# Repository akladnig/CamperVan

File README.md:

# CamperVan Design and Arduino Circuit Design

<!--toc:start-->
- [CamperVan Design and Arduino Circuit Design](#campervan-design-and-arduino-circuit-design)
  - [Campervan Design Overview](#campervan-design-overview)
  - [Dashboard App](#dashboard-app)
  - [Electrical System](#electrical-system)
    - [Sensors](#sensors)
  - [Circuit Design](#circuit-design)
    - [Battery and voltage monitoring](#battery-and-voltage-monitoring)
      - [Voltage Divider Design](#voltage-divider-design)
      - [Low Pass Filter](#low-pass-filter)
  - [TODO](#todo)
<!--toc:end-->

## Campervan Design Overview
I used [OpenScad](https://openscad.org/) to do the campervan design. Whilst I have used SketchUp in the past OpenScad appealed to me more as it is a programmers CAD program plus it is a parametric CAD program which allow me to quickly change a parameter to see how it affects the van layout e.g. visualising the Sofa Bed as a Sofa or a Bed, or easily changing the width of a cupboard, which would cause all other dependent cupboards to adjust accordingly.

## Dashboard App
The dashboard app on ios/macos to control the electrical system is written in Flutter and communicates to the Arduino control board via websockets. See [Campervan Flutter](https://github.com/akladnig/campervan_flutter) for details.

## Electrical System

The electrical system for the camper van needs to power the following devices:
- Induction Cooktop - 1800W
- Air Fryer - 1800W
- Duetto Hot Water - 300W
- Bushman 85l fridge -
- Water Pump -
- Lights & Fan - 

The power system needs to provide off-grid power for 3 days, which required a 4.8kW or 400Ah battery system.

Since 12V, 400A would require massive fuses, switches and cable etc. I've decided to run the system as 2x isolated batteries, rather than in parallel. This will reduce the need for 400A fuses and switches to 200A fuses ans switches.

The other issue is that the DC-DC battery charger has a maximum output of 50A which would result in a 7-8 hour charge time via the alternator. Being able to independently charge each battery with it's own battery charger solves this problem and also 2x 50A chargers are a lot cheaper than a single 100A charger.

The system is designed so the batteries can never be inadvertently connected in parallel.

There are two modes of operation:
- Manual
- Automatic

Manual mode will override any automatic setting and allows the selection of:
- which battery to use for powering appliances
- swapping the dc-dc battery chargers. This will allow selection of which battery to charge via Solar Cells/50A DC-DC charger or 20A DC-DC charger.

Automatic mode will select the battery to use for powering appliances. When the battery charge falls below a certain threshold it will swap to the other battery.

Automatic mode will also swap chargers during driving to ensure the optimum charge time for both batteries. When the ignition is off, charging via solar cells will automatically switch to the second battery when the first is fully charged.

### Sensors
There are a variety of sensors in use:
- voltage dividers
- RS485 which will require some reverse engineering
- Hall effect devices
- Bluetooth for the smart batteries and 50A DC-DC

The following devices are monitored for the associated properties using a voltage divider:
- Starter Battery voltage
- Battery 1 input voltage (before 60A fuse)
- Battery 1 output voltage (after 200A fuse)
- Battery 2 input voltage (before 60A fuse)
- Battery 2 output voltage (after 200A fuase)
- Battery 2 charge switch status - to a digital input
- Battery 2 switch status - to a digital input

The following are monitored via RS485:
- 20A DC-DC battery charger
- Duoetto Heater

The following are monitored via hall effect devices:
- Water input flow
- Water output flow

The following devices are bluetooth enabled:
- Battery 1
- Battery 2
- 50A DC-DC charger

Schematic design software used is [Kicad](https://www.kicad.org/)

## Circuit Design
### General Design requirements
- All inputs and outputs of the main management module to be optically isolated to prevent any issues with voltage spikes damaging the module and to also reduce any potential issues with ground loops and noise.

### Battery and voltage monitoring
#### Linear OptoCoupler Design
An IL300 linear opto-coupler is used to monitor the voltage of the following:
- Starter Battery
- Battery 1
- Battery 2

#### Voltage Divider Design
The typical battery voltage ranges from 10.0V - 14.4V and the maximum input voltage levels are ether 3.3V or 5V depending on the Arduino device used.
In order to keep power consumption low large value resistors in the 100k range will be used. But with such large values noise increases (Johnson noise) and the inputs to the ADC on the Arduino or external ADC (MCP3008 or MCP3208) require a low impedance source so a unity gain low pass filter will be required.

Equation for the voltage divider is:

R1 = R2(Vin - Vout)/Vout

Using an input voltage of 15.0V and choosing R2 = 100k
Gives:

- R1 = 357k 1% for a 3.3V output
- R1 = 200k 1% for a 5V output

#### Low Pass Filter
A simple 2 pole Butterworth low pass filter will be used.
A quick web search shows that a 0.1Hz - 1Hz filter should be used, which sounds reasonable to me. I'll use 1Hz to keep the capacitor value on the lower end.

Formula for a low pass filter is:
- RC = 1/(2\*pi\*Cn\*f)

Cn and K are constants that are used to set various low pass filter types. For a 2 pole Butterworth the values are:
- Cn = 1
- K = 1.586

Refer to "The Art of Electronics page 408".

For:
- f = 1Hz
- C = 1uF

Gives:
- R = 154k 1%
- Rga = (K-1)R = 5k9 1% 

## TODO
 - add an Oled touch panel
 - ignition switch input

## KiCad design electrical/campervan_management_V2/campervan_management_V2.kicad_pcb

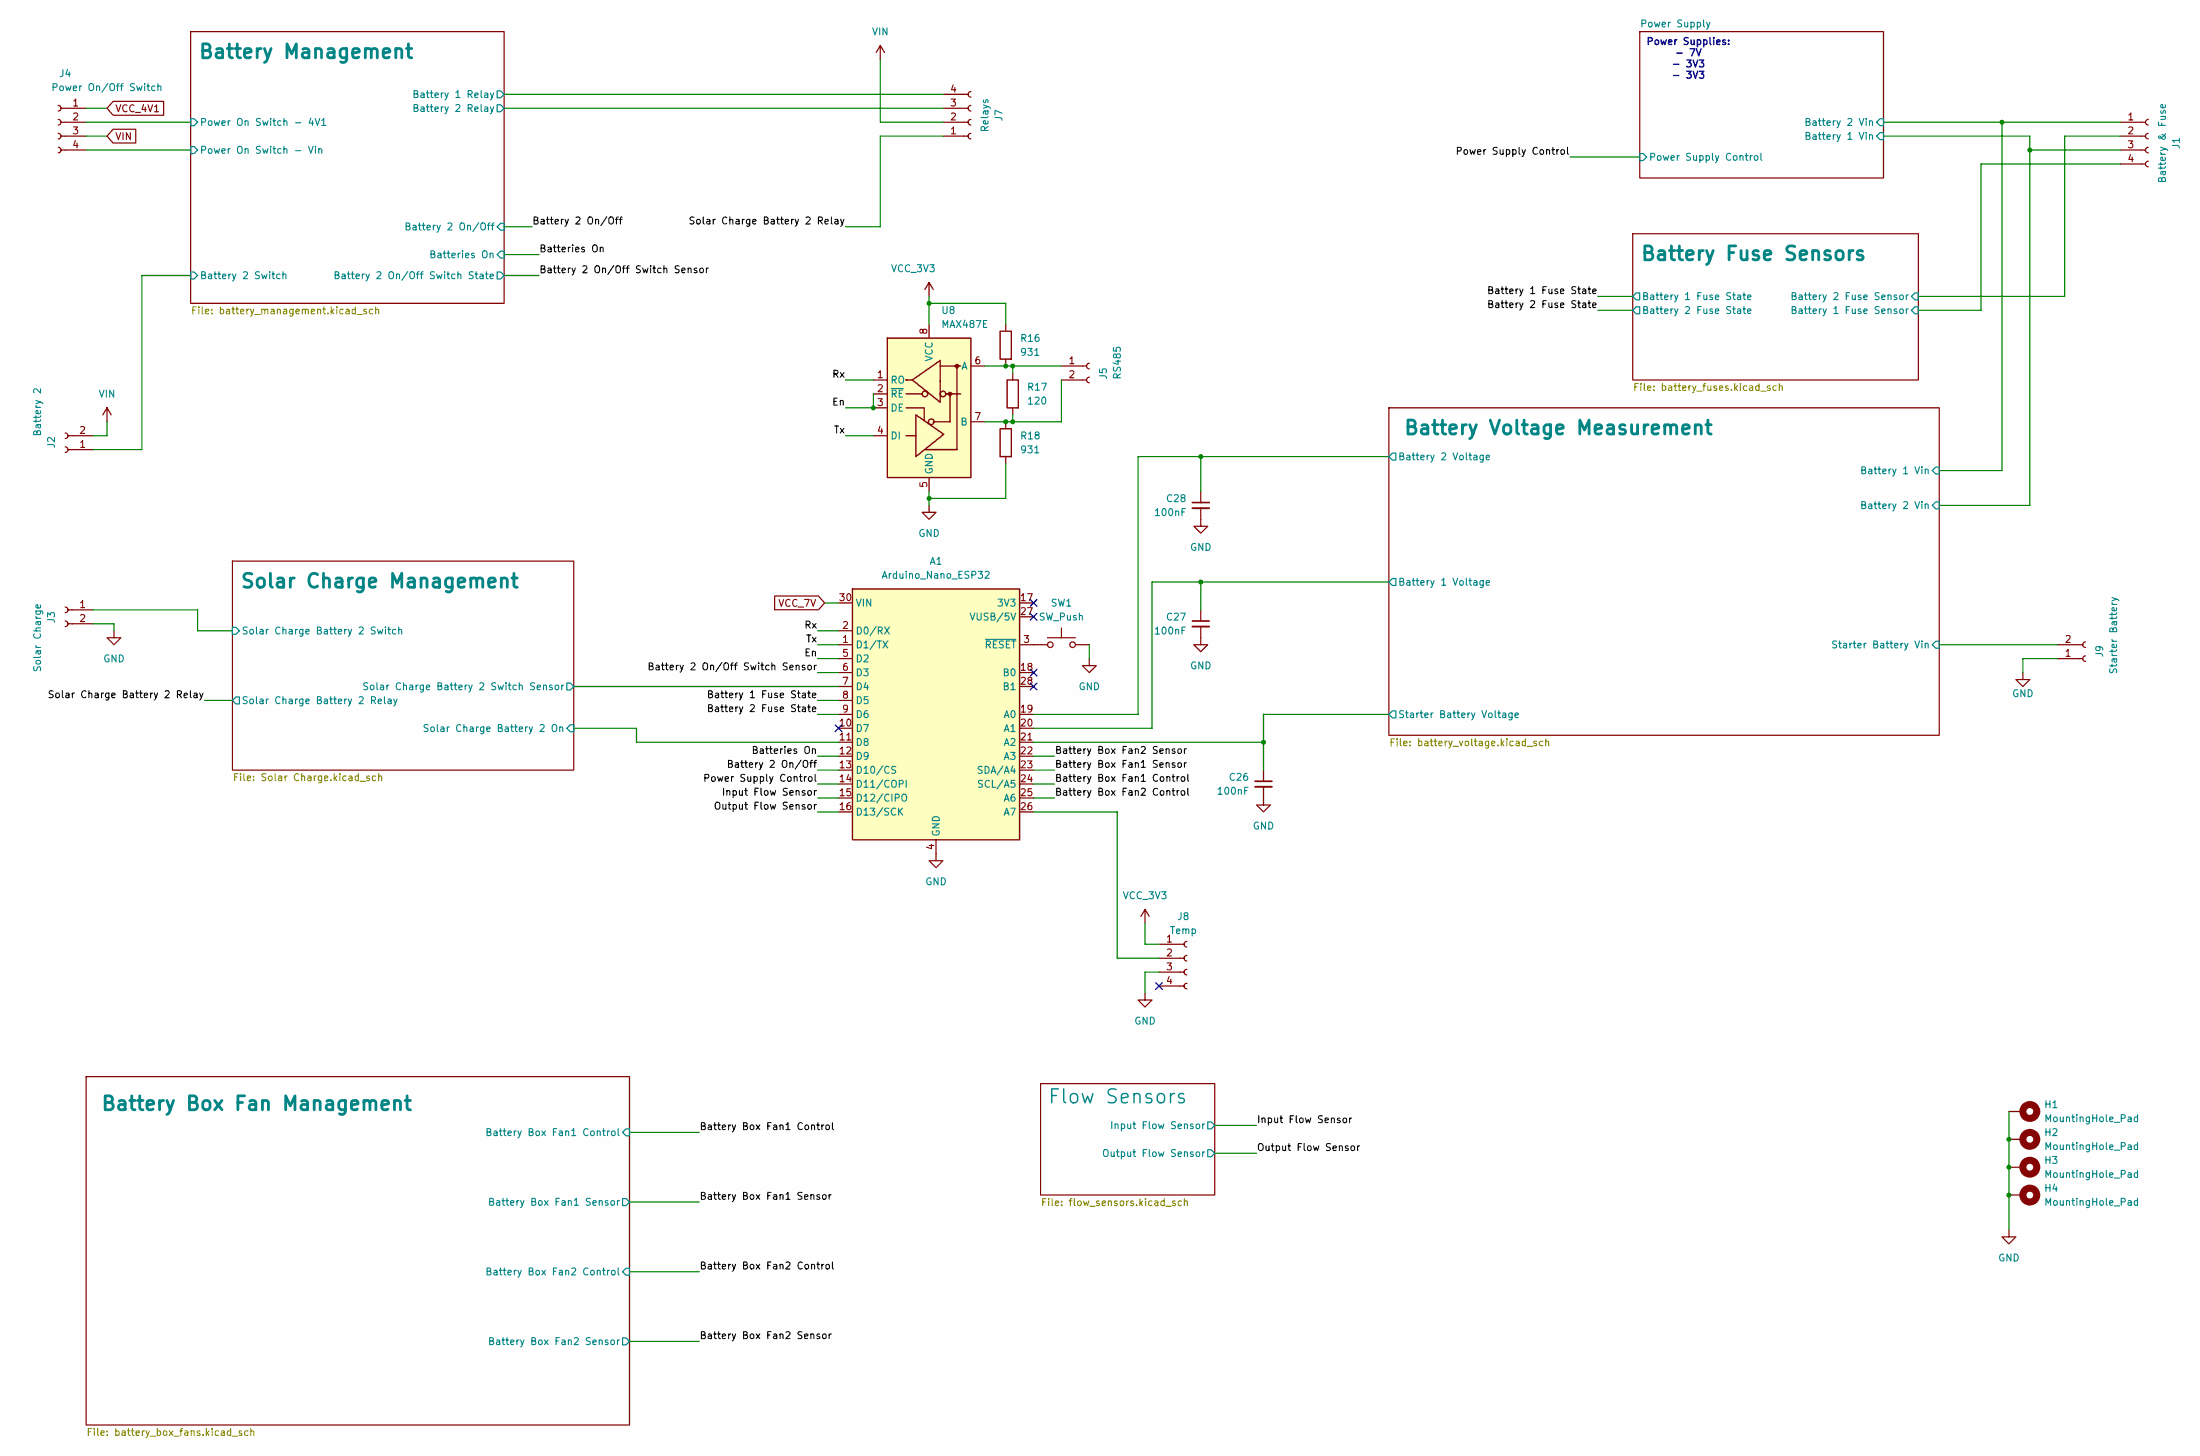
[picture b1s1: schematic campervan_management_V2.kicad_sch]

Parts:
A1: Arduino_Nano_ESP32; Arduino_Nano
C26, C27, C28: 100nF; C_0805_2012Metric; LCSC PN C28233
H1, H2, H3, H4: MountingHole_Pad; MountingHole_4.3mm_M4_Pad
J1: Battery & Fuse; Molex_Mini-Fit_Jr_5566-04A_2x02_P4.20mm_Vertical
J2: Battery 2; Molex_Mini-Fit_Jr_5566-02A_2x01_P4.20mm_Vertical
J3: Solar Charge; Molex_Mini-Fit_Jr_5566-02A_2x01_P4.20mm_Vertical
J4: Power On/Off Switch; Molex_Mini-Fit_Jr_5566-04A_2x02_P4.20mm_Vertical
J5: RS485; Molex_Mini-Fit_Jr_5566-02A_2x01_P4.20mm_Vertical
J7: Relays; Molex_Mini-Fit_Jr_5566-04A_2x02_P4.20mm_Vertical
J8: Temp; Molex_Mini-Fit_Jr_5566-04A_2x02_P4.20mm_Vertical
J9: Starter Battery; Molex_Mini-Fit_Jr_5566-02A_2x01_P4.20mm_Vertical
R16, R18: 931; R_0805_2012Metric
R17: 120; R_0805_2012Metric; LCSC PN C17437
SW1: SW_Push; SW_SPST_JLC; LCSC PN C720477
U8: MAX487E; SOIC-8_3.9x4.9mm_P1.27mm; LCSC PN C116539

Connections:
/Batteries On: A1.12 (D9); also elsewhere on the board
/Battery 1 Fuse State: A1.8 (D5); also elsewhere on the board
/Battery 2 Fuse State: A1.9 (D6); also elsewhere on the board
/Battery 2 On/Off: A1.13 (D10/CS); also elsewhere on the board
/Battery 2 On/Off Switch Sensor: A1.6 (D3); also elsewhere on the board
/Battery Box Fan1 Control: A1.24 (SCL/A5); also elsewhere on the board
/Battery Box Fan1 Sensor: A1.23 (SDA/A4); also elsewhere on the board
/Battery Box Fan2 Control: A1.25 (A6); also elsewhere on the board
/Battery Box Fan2 Sensor: A1.22 (A3); also elsewhere on the board
/Battery Fuse Sensors/Battery 1 Fuse Sensor: J1.4; also elsewhere on the board
/Battery Fuse Sensors/Battery 2 Fuse Sensor: J1.2; also elsewhere on the board
/Battery Management/Battery 1 Relay: J7.4; also elsewhere on the board
/Battery Management/Battery 2 Relay: J7.3; also elsewhere on the board
/Battery Management/Battery 2 Switch: J2.1; also elsewhere on the board
/Battery Management/Power On Switch - 4V1: J4.2; also elsewhere on the board
/Battery Management/Power On Switch - Vin: J4.4; also elsewhere on the board
/Battery Voltage Measurement/Battery 1 Vin: J1.1; also elsewhere on the board
/Battery Voltage Measurement/Battery 1 Voltage: A1.20 (A1), C27.1; also elsewhere on the board
/Battery Voltage Measurement/Battery 2 Vin: J1.3; also elsewhere on the board
/Battery Voltage Measurement/Battery 2 Voltage: A1.19 (A0), C28.1; also elsewhere on the board
/Battery Voltage Measurement/Starter Battery Vin: J9.2; also elsewhere on the board
/Battery Voltage Measurement/Starter Battery Voltage: A1.21 (A2), C26.1; also elsewhere on the board
/En: A1.5 (D2), U8.2 (~RE), U8.3 (DE)
/Input Flow Sensor: A1.15 (D12/CIPO); also elsewhere on the board
/Output Flow Sensor: A1.16 (D13/SCK); also elsewhere on the board
/Power Supply Control: A1.14 (D11/COPI); also elsewhere on the board
/Rx: A1.2 (D0/RX), U8.1 (RO)
/Solar Charge Battery 2 Relay: J7.1; also elsewhere on the board
/Solar Charge Management/Solar Charge Battery 2 On: A1.11 (D8); also elsewhere on the board
/Solar Charge Management/Solar Charge Battery 2 Switch: J3.1; also elsewhere on the board
/Solar Charge Management/Solar Charge Battery 2 Switch Sensor: A1.7 (D4); also elsewhere on the board
/Tx: A1.1 (D1/TX), U8.4 (DI)
GND: A1.4 (GND), A1.29 (GND), C26.2, C27.2, C28.2, H1.1, H2.1, H3.1, H4.1, J3.2, J8.3, J9.1, R18.2, SW1.2, U8.5 (GND); also elsewhere on the board
unnamed: A1.26 (A7), J8.2
unnamed: A1.3 (~RESET), SW1.1
unnamed: J5.1, R16.2, R17.1, U8.6 (A)
unnamed: J5.2, R17.2, R18.1, U8.7 (B)
VCC_3V3: J8.1, R16.1, U8.8 (VCC); also elsewhere on the board
VCC_4V1: J4.1; also elsewhere on the board
VCC_7V: A1.30 (VIN); also elsewhere on the board
VIN: J2.2, J4.3, J7.2; also elsewhere on the board

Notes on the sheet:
Power Supplies: - 7V - 3V3 - 3V3

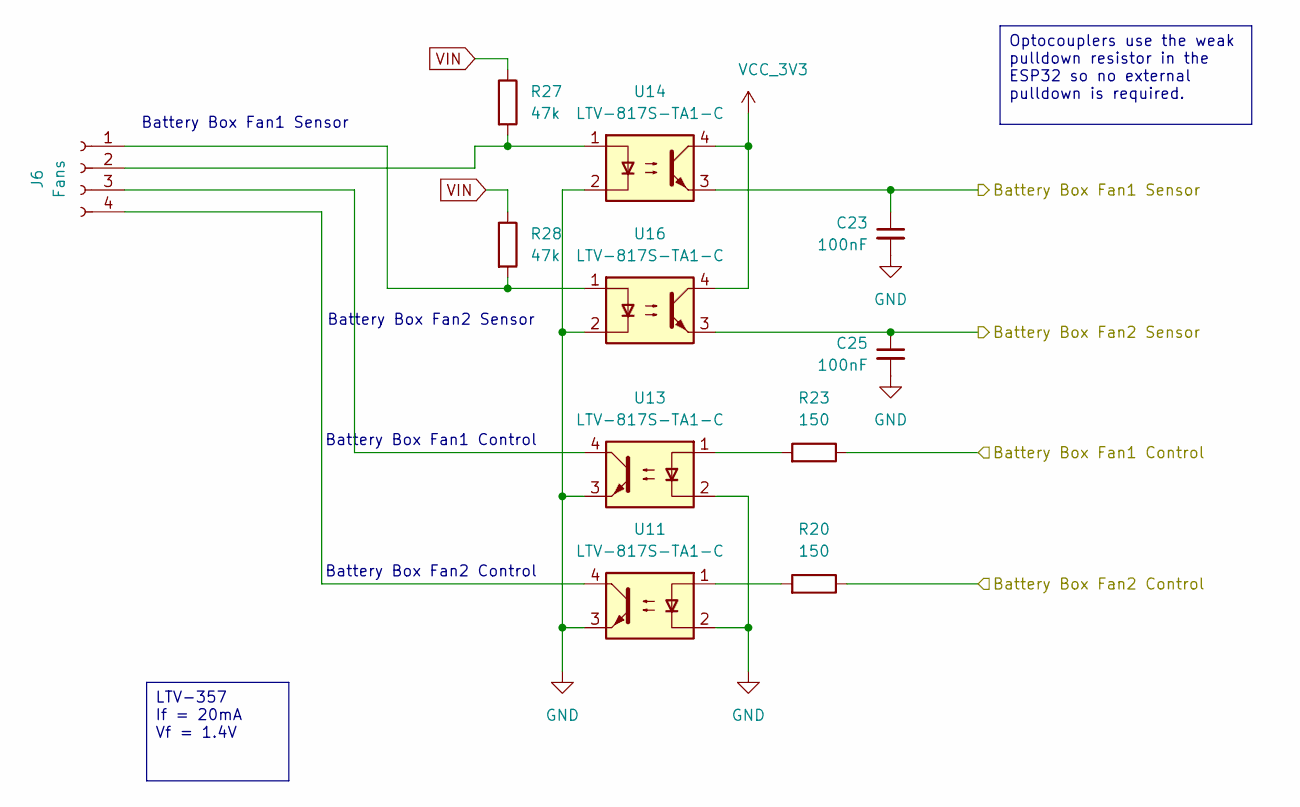
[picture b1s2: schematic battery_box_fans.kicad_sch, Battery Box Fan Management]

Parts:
C23, C25: 100nF; C_0805_2012Metric; LCSC PN C28233
J6: Fans; Molex_Mini-Fit_Jr_5566-04A_2x02_P4.20mm_Vertical
R20, R23: 150; R_0805_2012Metric; LCSC PN C17471
R27, R28: 47k; R_0805_2012Metric; LCSC PN C17713
U11, U13, U14, U16: LTV-817S-TA1-C; SO-4_4.4x3.6mm_P2.54mm; LCSC PN C109227

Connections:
/Battery Box Fan1 Control: R23.1; also elsewhere on the board
/Battery Box Fan1 Sensor: C23.1, U14.3; also elsewhere on the board
/Battery Box Fan2 Control: R20.1; also elsewhere on the board
/Battery Box Fan2 Sensor: C25.1, U16.3; also elsewhere on the board
GND: C23.2, C25.2, U11.2, U11.3, U13.2, U13.3, U14.2, U16.2; also elsewhere on the board
unnamed: J6.1, R28.2, U16.1
unnamed: J6.2, R27.2, U14.1
unnamed: J6.3, U13.4
unnamed: J6.4, U11.4
unnamed: R20.2, U11.1
unnamed: R23.2, U13.1
VCC_3V3: U14.4, U16.4; also elsewhere on the board
VIN: R27.1, R28.1; also elsewhere on the board

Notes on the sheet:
Battery Box Fan2 Control
Battery Box Fan1 Control
Battery Box Fan2 Sensor
Battery Box Fan1 Sensor
Optocouplers use the weak pulldown resistor in the ESP32 so no external pulldown is required.
LTV-357 If = 20mA Vf = 1.4V

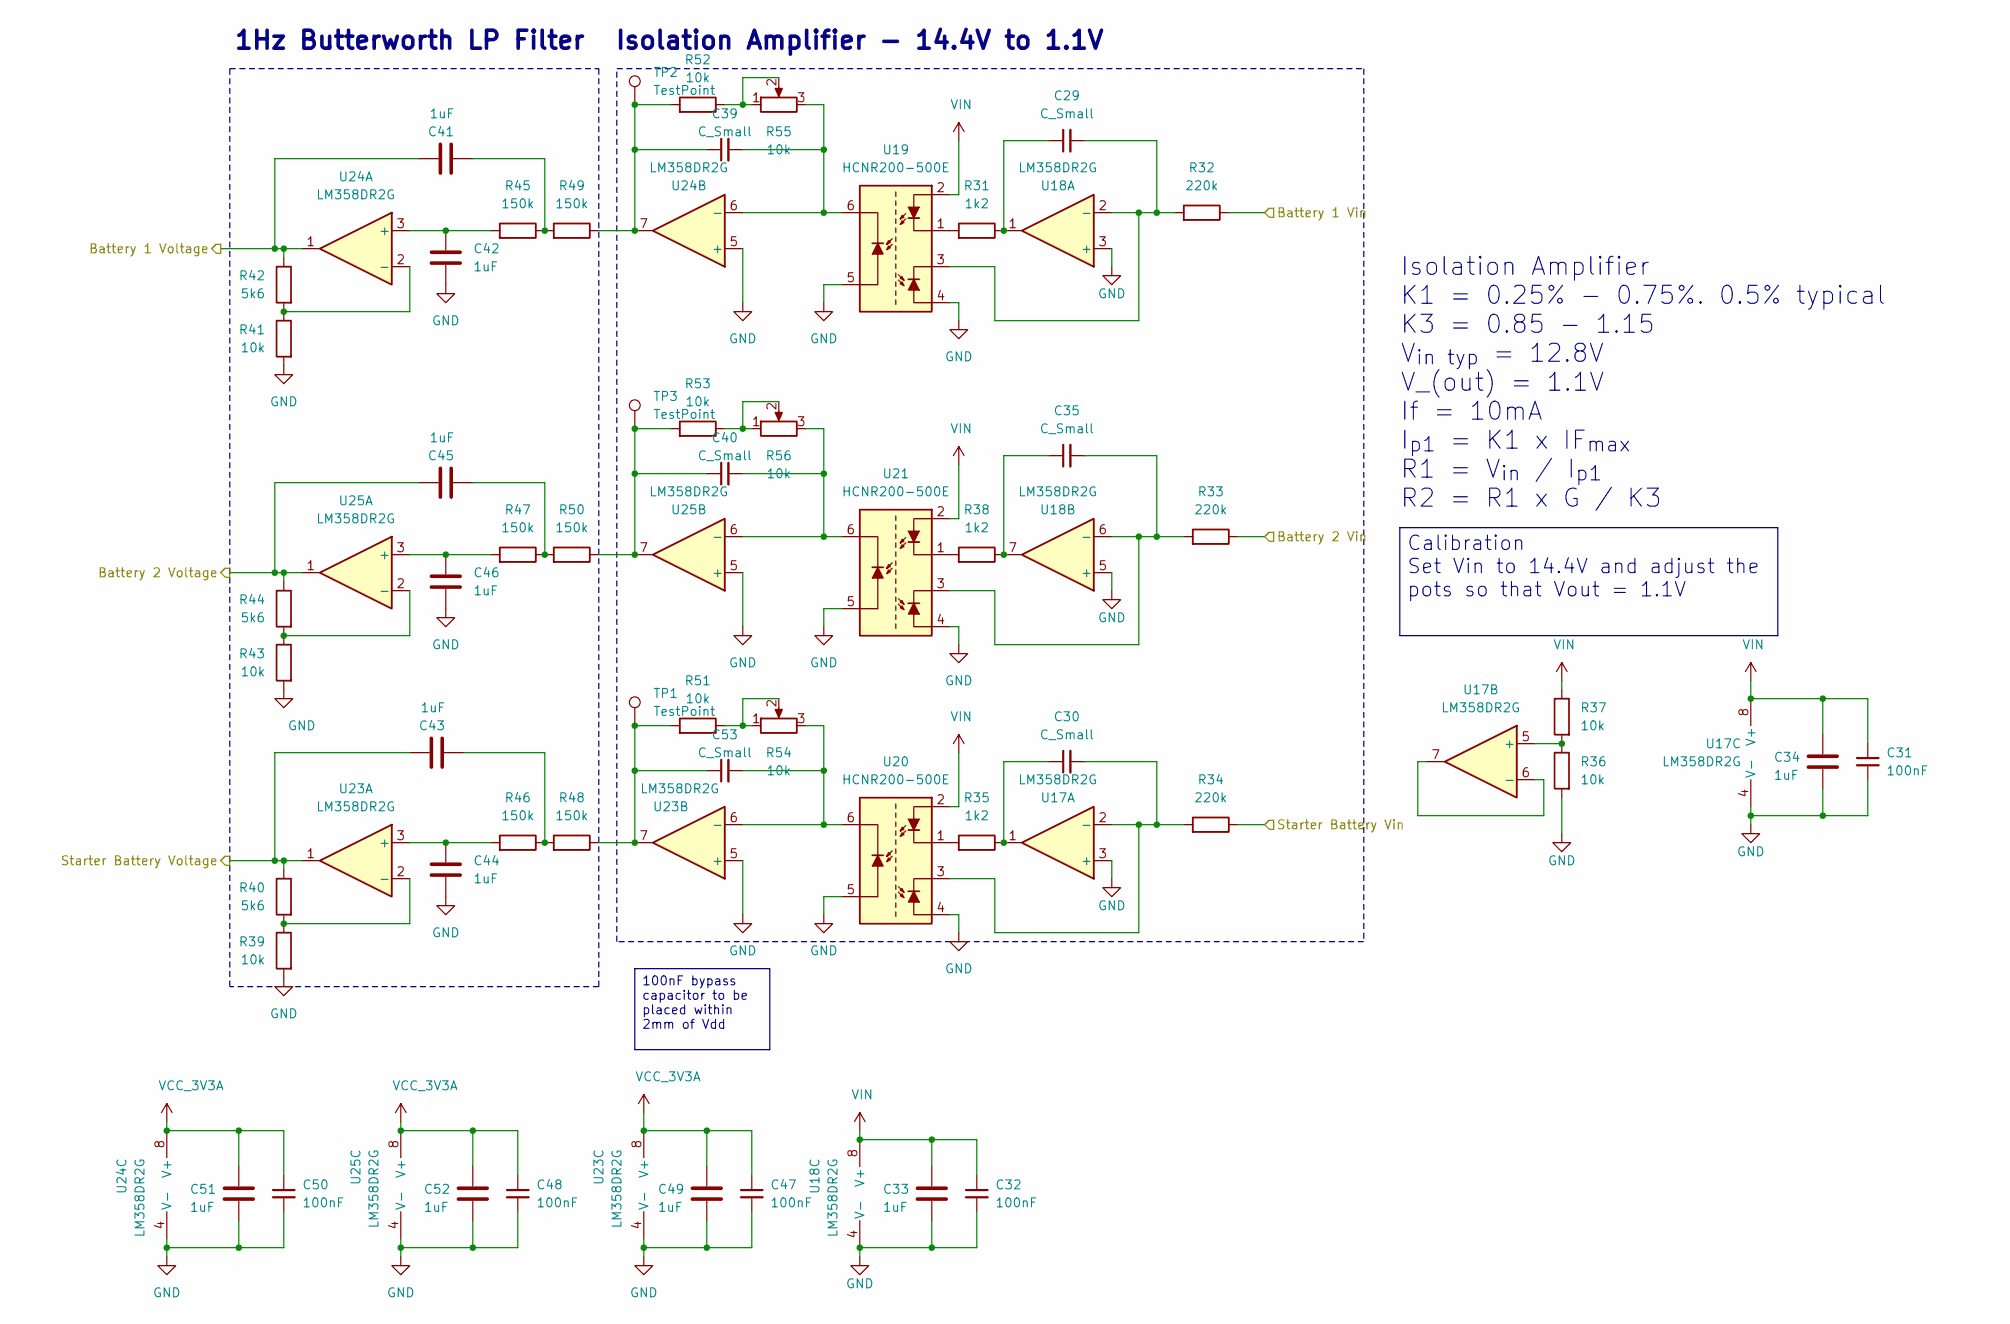
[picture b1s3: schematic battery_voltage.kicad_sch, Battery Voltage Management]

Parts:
C29, C30, C35, C39, C40, C53: C_Small; C_0603_1608Metric
C31, C32, C47, C48, C50: 100nF; C_0805_2012Metric; LCSC PN C28233
C33, C34, C41, C42, C43, C44, C45, C46, C49, C51, C52: 1uF; C_0603_1608Metric; LCSC PN C15849
R31, R35, R38: 1k2; R_0603_1608Metric; LCSC PN C22765
R32, R33, R34: 220k; R_0603_1608Metric; LCSC PN C22967
R36, R37, R39, R41, R43, R51, R52, R53: 10k; R_0603_1608Metric; LCSC PN C25804
R40, R42, R44: 5k6; R_0603_1608Metric; LCSC PN C23189
R45, R46, R47, R48, R49, R50: 150k; R_0603_1608Metric; LCSC PN C22807
R54, R55, R56: 10k; Potentiometer_Bourns_3296W_Vertical
TP1, TP2, TP3: TestPoint; 5000
U17, U18, U23, U24, U25: LM358DR2G; SOIC-8_ONS-L; LCSC PN C7950
U19, U20, U21: HCNR200-500E; SMDIP-8_W11.48mm; LCSC PN C23785

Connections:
/Battery Voltage Measurement/Battery 1 Vin: R32.1; also elsewhere on the board
/Battery Voltage Measurement/Battery 1 Voltage: C41.2, R42.1, U24.1; also elsewhere on the board
/Battery Voltage Measurement/Battery 2 Vin: R33.1; also elsewhere on the board
/Battery Voltage Measurement/Battery 2 Voltage: C45.2, R44.1, U25.1; also elsewhere on the board
/Battery Voltage Measurement/Starter Battery Vin: R34.1; also elsewhere on the board
/Battery Voltage Measurement/Starter Battery Voltage: C43.2, R40.1, U23.1; also elsewhere on the board
GND: C31.2, C32.2, C33.2, C34.2, C42.2, C44.2, C46.2, C47.2, C48.2, C49.2, C50.2, C51.2, C52.2, R36.2, R39.2, R41.2, R43.2, U17.3 (+), U17.4 (V-), U18.3 (+), U18.4 (V-), U18.5 (+), U19.4, U19.5, U20.4, U20.5, U21.4, U21.5, U23.4 (V-), U23.5 (+), U24.4 (V-), U24.5 (+), U25.4 (V-), U25.5 (+); also elsewhere on the board
unnamed: C29.1, R31.1, U18.1
unnamed: C30.1, R35.1, U17.1
unnamed: C35.1, R38.1, U18.7
unnamed: C39.1, R49.1, R52.2, TP2.1, U24.7
unnamed: C40.1, R50.1, R53.2, TP3.1, U25.7
unnamed: C41.1, R45.1, R49.2
unnamed: C43.1, R46.1, R48.2
unnamed: C45.1, R47.1, R50.2
unnamed: C53.1, R48.1, R51.2, TP1.1, U23.7
unnamed: R31.2, U19.1
unnamed: R35.2, U20.1
unnamed: R38.2, U21.1
unnamed: R51.1, R54.1, R54.2
unnamed: R52.1, R55.1, R55.2
unnamed: R53.1, R56.1, R56.2
unnamed: C30.2, R34.2, U17.2 (-), U20.3
unnamed: R36.1, R37.2, U17.5 (+)
unnamed: U17.6 (-), U17.7
unnamed: C29.2, R32.2, U18.2 (-), U19.3
unnamed: C35.2, R33.2, U18.6 (-), U21.3
unnamed: C44.1, R46.2, U23.3 (+)
unnamed: R39.1, R40.2, U23.2 (-)
unnamed: C53.2, R54.3, U20.6, U23.6 (-)
unnamed: C42.1, R45.2, U24.3 (+)
unnamed: R41.1, R42.2, U24.2 (-)
unnamed: C39.2, R55.3, U19.6, U24.6 (-)
unnamed: C46.1, R47.2, U25.3 (+)
unnamed: R43.1, R44.2, U25.2 (-)
unnamed: C40.2, R56.3, U21.6, U25.6 (-)
VCC_3V3A: C47.1, C48.1, C49.1, C50.1, C51.1, C52.1, U23.8 (V+), U24.8 (V+), U25.8 (V+); also elsewhere on the board
VIN: C31.1, C32.1, C33.1, C34.1, R37.1, U17.8 (V+), U18.8 (V+), U19.2, U20.2, U21.2; also elsewhere on the board

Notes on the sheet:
Isolation Amplifier K1 = 0.25% - 0.75%. 0.5% typical K3 = 0.85 - 1.15 V_{in typ} = 12.8V V_(out) = 1.1V If = 10mA I_{p1} = K1 x IF_{max} R1 = V_{in} / I_{p1} R2 = R1 x G / K3
Isolation Amplifier - 14.4V to 1.1V
1Hz Butterworth LP Filter
100nF bypass capacitor to be placed within 2mm of Vdd
Calibration Set Vin to 14.4V and adjust the pots so that Vout = 1.1V

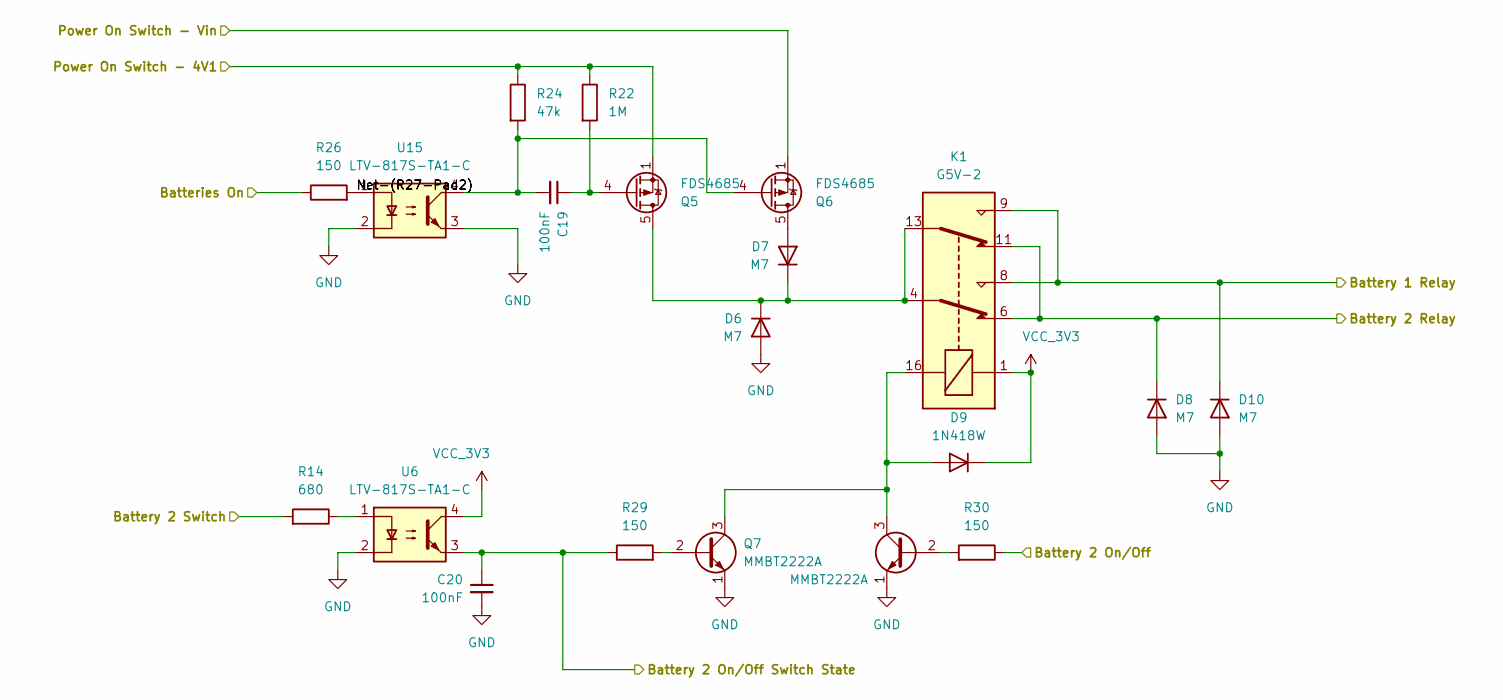
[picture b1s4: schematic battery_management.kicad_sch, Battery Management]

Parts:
C19, C20: 100nF; C_0805_2012Metric; LCSC PN C28233
D6, D7, D8, D10: M7; D_SMA; LCSC PN C95872
D9: 1N418W; D_SOD-123; LCSC PN C81598
K1: G5V-2; Relay_DPDT_Omron_G5V-2
Q5, Q6: FDS4685; SOIC-8_3.9x4.9mm_P1.27mm; LCSC PN C336026
Q7, Q8: MMBT2222A; SOT-23; LCSC PN C8512
R14: 680; R_0805_2012Metric; LCSC PN C17798
R22: 1M; R_0805_2012Metric; LCSC PN C17514
R24: 47k; R_0805_2012Metric; LCSC PN C17713
R26, R29, R30: 150; R_0805_2012Metric; LCSC PN C17471
U6, U15: LTV-817S-TA1-C; SO-4_4.4x3.6mm_P2.54mm; LCSC PN C109227

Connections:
/Batteries On: R26.1; also elsewhere on the board
/Battery 2 On/Off: R30.1; also elsewhere on the board
/Battery 2 On/Off Switch Sensor: C20.1, R29.1, U6.3; also elsewhere on the board
/Battery Management/Battery 1 Relay: D10.1 (K), K1.8, K1.9; also elsewhere on the board
/Battery Management/Battery 2 Relay: D8.1 (K), K1.6, K1.11; also elsewhere on the board
/Battery Management/Battery 2 Switch: R14.2; also elsewhere on the board
/Battery Management/Net-(R27-Pad2): R26.2, U15.1
/Battery Management/Power On Switch - 4V1: Q5.1 (S), Q5.2 (S), Q5.3 (S), R22.1, R24.1; also elsewhere on the board
/Battery Management/Power On Switch - Vin: Q6.1 (S), Q6.2 (S), Q6.3 (S); also elsewhere on the board
GND: C20.2, D6.2 (A), D8.2 (A), D10.2 (A), Q7.1 (E), Q8.1 (E), U6.2, U15.2, U15.3; also elsewhere on the board
unnamed: D6.1 (K), D7.1 (K), K1.4, K1.13, Q5.5 (D), Q5.6 (D), Q5.7 (D), Q5.8 (D)
unnamed: D7.2 (A), Q6.5 (D), Q6.6 (D), Q6.7 (D), Q6.8 (D)
unnamed: D9.2 (A), K1.16, Q7.3 (C), Q8.3 (C)
unnamed: C19.1, Q5.4 (G), R22.2
unnamed: C19.2, Q6.4 (G), R24.2, U15.4
unnamed: Q7.2 (B), R29.2
unnamed: Q8.2 (B), R30.2
unnamed: R14.1, U6.1
VCC_3V3: D9.1 (K), K1.1, U6.4; also elsewhere on the board

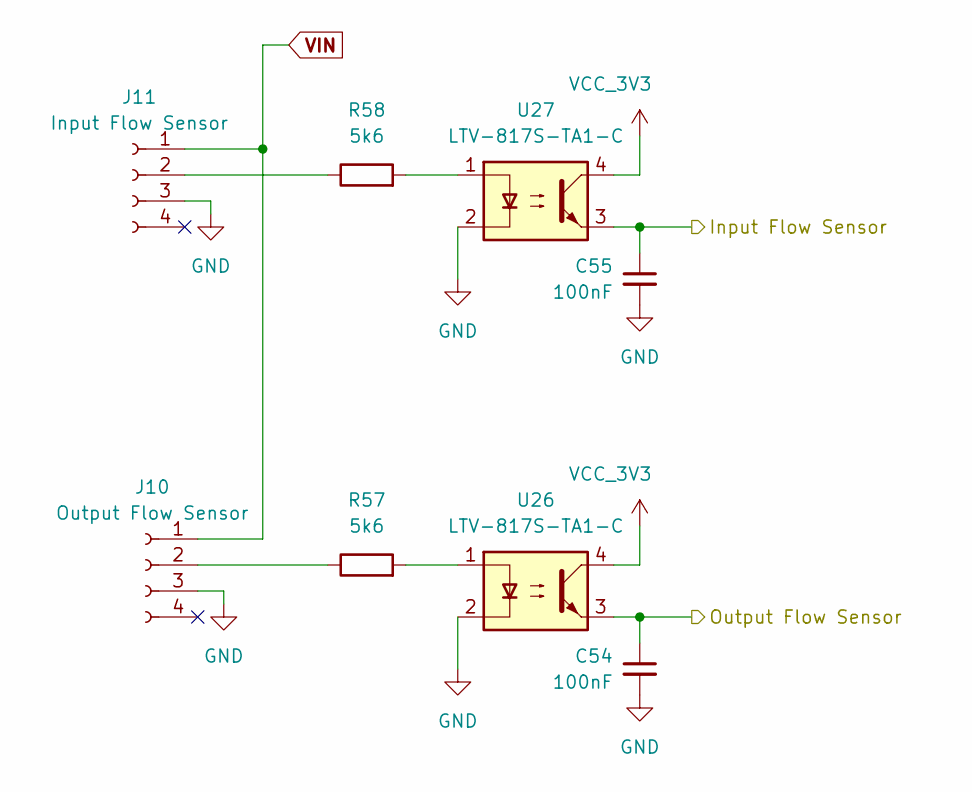
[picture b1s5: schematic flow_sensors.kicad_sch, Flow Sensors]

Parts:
C54, C55: 100nF; C_0805_2012Metric; LCSC PN C28233
J10: Output Flow Sensor; Molex_Mini-Fit_Jr_5566-04A_2x02_P4.20mm_Vertical
J11: Input Flow Sensor; Molex_Mini-Fit_Jr_5566-04A_2x02_P4.20mm_Vertical
R57, R58: 5k6; R_0603_1608Metric
U26, U27: LTV-817S-TA1-C; SO-4_4.4x3.6mm_P2.54mm; LCSC PN C109227

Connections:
/Input Flow Sensor: C55.1, U27.3; also elsewhere on the board
/Output Flow Sensor: C54.1, U26.3; also elsewhere on the board
GND: C54.2, C55.2, J10.3, J11.3, U26.2, U27.2; also elsewhere on the board
unnamed: J11.2, R58.1
unnamed: J10.2, R57.1
unnamed: R58.2, U27.1
unnamed: R57.2, U26.1
VCC_3V3: U26.4, U27.4; also elsewhere on the board
VIN: J10.1, J11.1; also elsewhere on the board

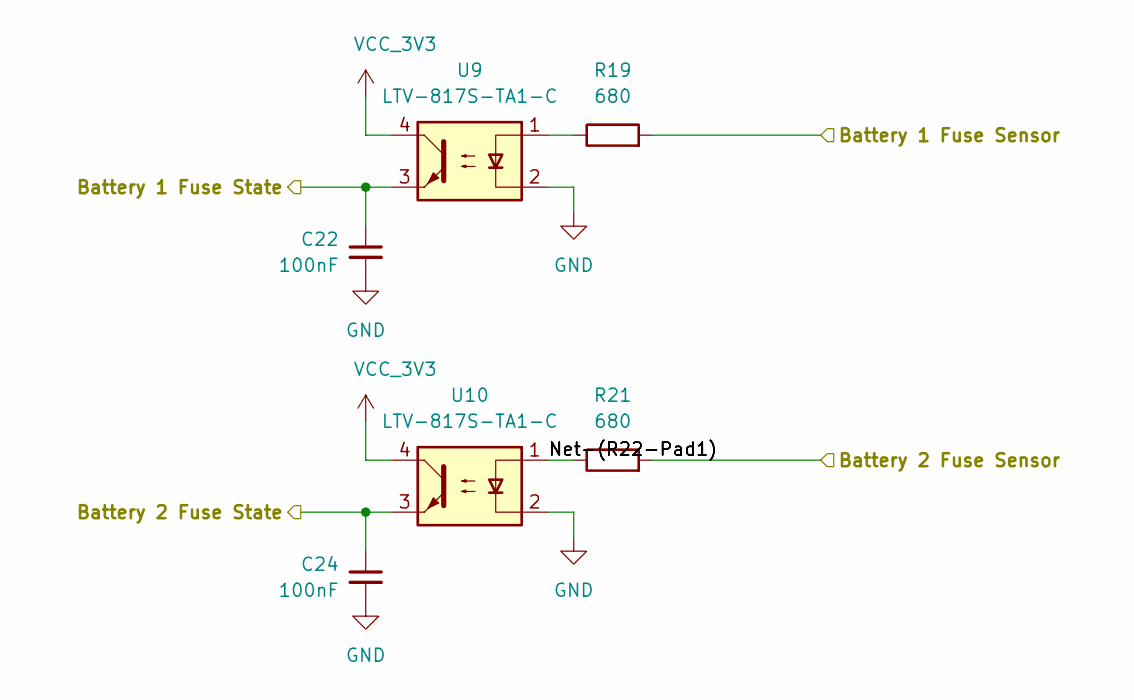
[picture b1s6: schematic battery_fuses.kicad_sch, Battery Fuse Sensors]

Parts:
C22, C24: 100nF; C_0805_2012Metric; LCSC PN C28233
R19, R21: 680; R_0805_2012Metric; LCSC PN C17798
U9, U10: LTV-817S-TA1-C; SO-4_4.4x3.6mm_P2.54mm; LCSC PN C109227

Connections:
/Battery 1 Fuse State: C22.1, U9.3; also elsewhere on the board
/Battery 2 Fuse State: C24.1, U10.3; also elsewhere on the board
/Battery Fuse Sensors/Battery 1 Fuse Sensor: R19.2; also elsewhere on the board
/Battery Fuse Sensors/Battery 2 Fuse Sensor: R21.2; also elsewhere on the board
/Battery Fuse Sensors/Net-(R22-Pad1): R21.1, U10.1
GND: C22.2, C24.2, U9.2, U10.2; also elsewhere on the board
unnamed: R19.1, U9.1
VCC_3V3: U9.4, U10.4; also elsewhere on the board

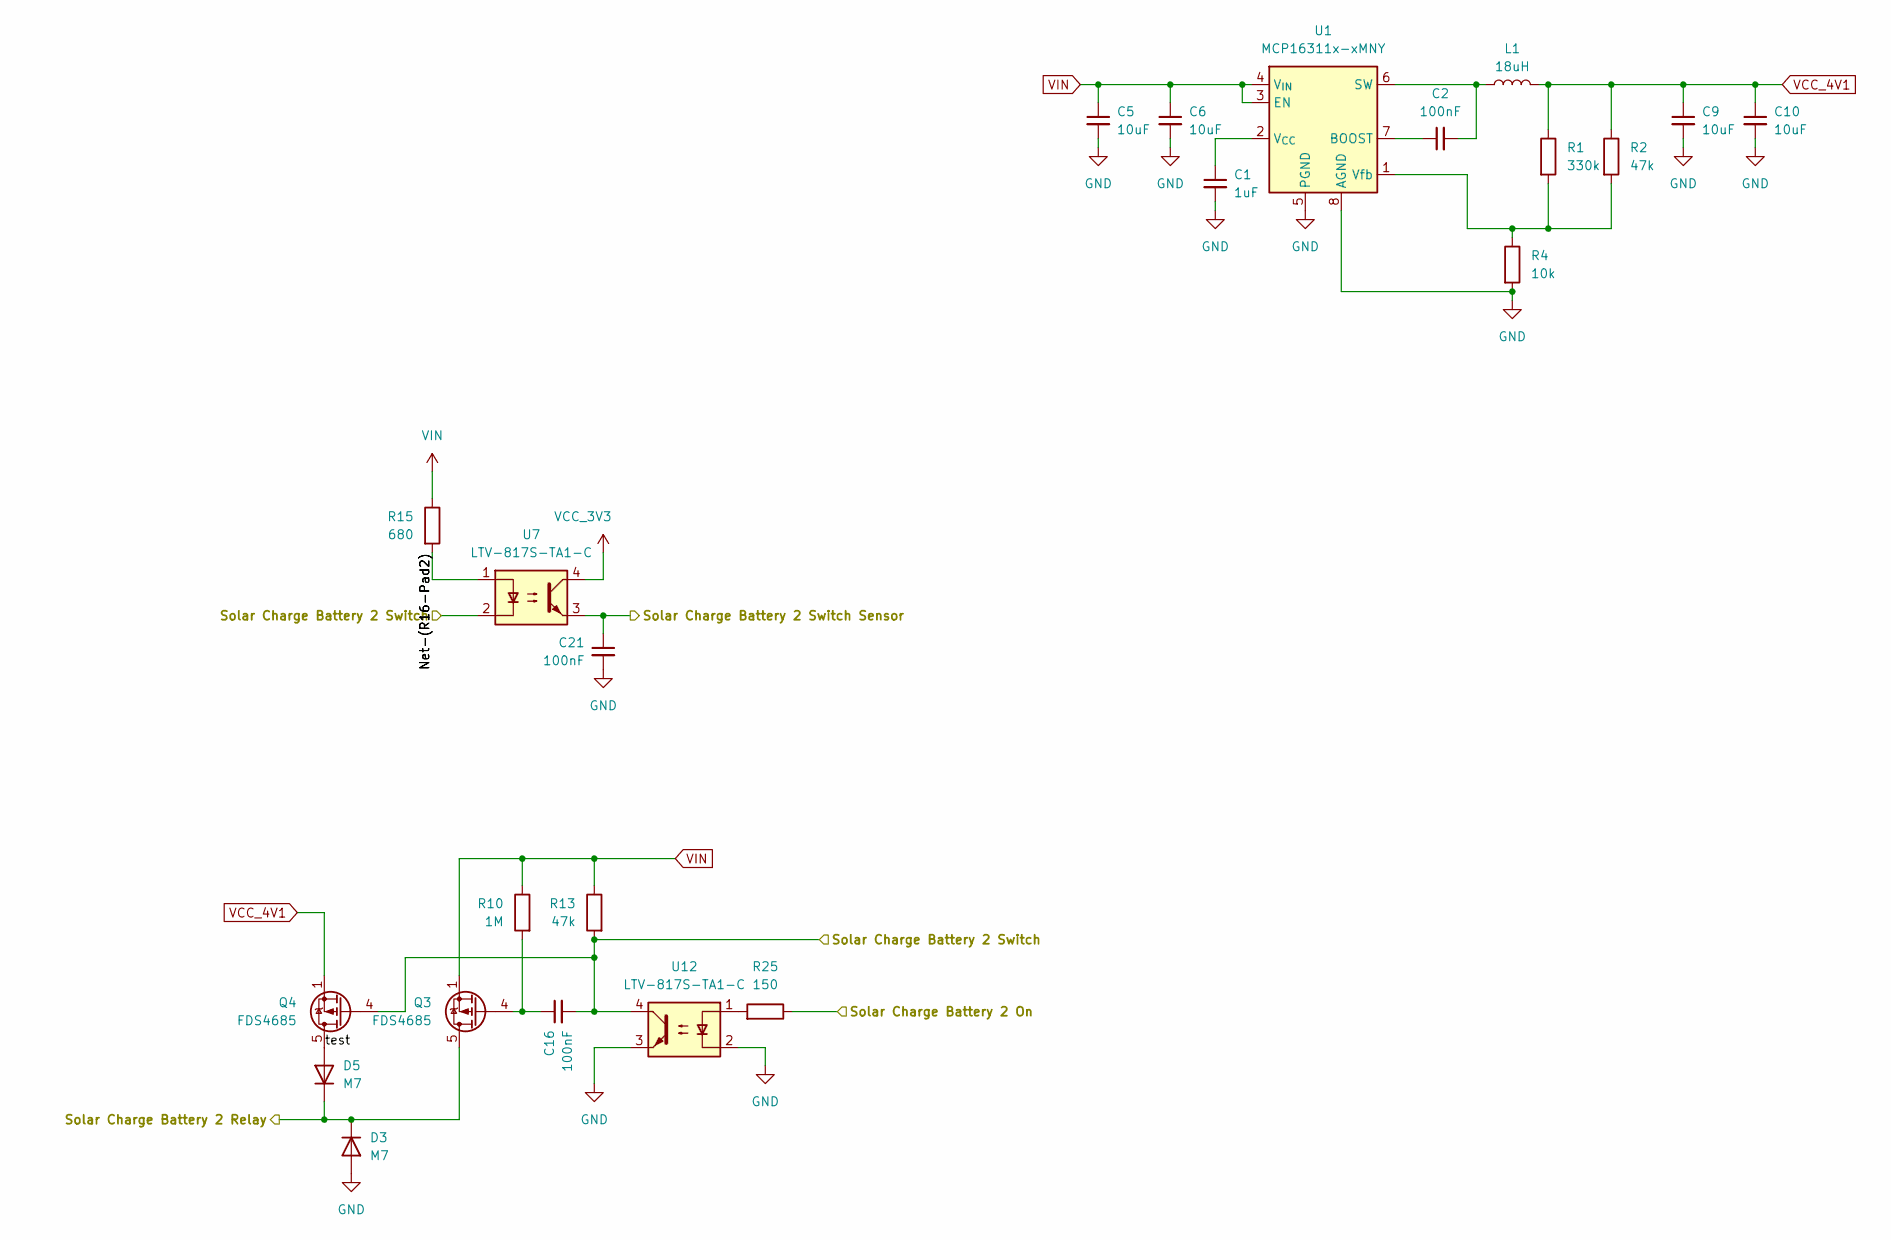
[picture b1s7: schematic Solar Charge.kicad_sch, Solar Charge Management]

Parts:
C1: 1uF; C_0603_1608Metric; LCSC PN C15849
C2, C16, C21: 100nF; C_0805_2012Metric; LCSC PN C28233
C5, C6, C9, C10: 10uF; C_1206_3216Metric; LCSC PN C13585
D3, D5: M7; D_SMA; LCSC PN C95872
L1: 18uH; L_Coilcraft_MSS1038-XXX
Q3, Q4: FDS4685; SOIC-8_3.9x4.9mm_P1.27mm; LCSC PN C336026
R1: 330k; R_0603_1608Metric; LCSC PN C23231
R2: 47k; R_0603_1608Metric; LCSC PN C25804
R4: 10k; R_0603_1608Metric; LCSC PN C25804
R10: 1M; R_0805_2012Metric; LCSC PN C17514
R13: 47k; R_0805_2012Metric; LCSC PN C17713
R15: 680; R_0805_2012Metric; LCSC PN C17798
R25: 150; R_0805_2012Metric; LCSC PN C17471
U1: MCP16311x-xMNY; DFN-8-1EP_3x2mm_P0.5mm_EP1.75x1.45mm; LCSC PN C510882
U7, U12: LTV-817S-TA1-C; SO-4_4.4x3.6mm_P2.54mm; LCSC PN C109227

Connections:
/Solar Charge Battery 2 Relay: D3.1 (K), D5.1 (K), Q3.5 (D), Q3.6 (D), Q3.7 (D), Q3.8 (D); also elsewhere on the board
/Solar Charge Management/Net-(R16-Pad2): R15.2, U7.1
/Solar Charge Management/Solar Charge Battery 2 On: R25.1; also elsewhere on the board
/Solar Charge Management/Solar Charge Battery 2 Switch: C16.2, Q4.4 (G), R13.2, U7.2, U12.4; also elsewhere on the board
/Solar Charge Management/Solar Charge Battery 2 Switch Sensor: C21.1, U7.3; also elsewhere on the board
/Solar Charge Management/test: D5.2 (A), Q4.5 (D), Q4.6 (D), Q4.7 (D), Q4.8 (D)
GND: C1.2, C5.2, C6.2, C9.2, C10.2, C21.2, D3.2 (A), R4.2, U1.5 (PGND), U1.8 (AGND), U1.9 (GND), U12.2, U12.3; also elsewhere on the board
unnamed: C16.1, Q3.4 (G), R10.2
unnamed: R25.2, U12.1
unnamed: C2.1, U1.7 (BOOST)
unnamed: C2.2, L1.1, U1.6 (SW)
unnamed: C1.1, U1.2 (V_{CC})
unnamed: R1.2, R2.2, R4.1, U1.1 (Vfb)
VCC_3V3: U7.4; also elsewhere on the board
VCC_4V1: C9.1, C10.1, L1.2, Q4.1 (S), Q4.2 (S), Q4.3 (S), R1.1, R2.1; also elsewhere on the board
VIN: C5.1, C6.1, Q3.1 (S), Q3.2 (S), Q3.3 (S), R10.1, R13.1, R15.1, U1.3 (EN), U1.4 (V_{IN}); also elsewhere on the board
